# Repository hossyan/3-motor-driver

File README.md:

# 3-motor-driver
PWM信号を送ってモータを一つ動かすための回路です。
大きめの電流が流れる線が細いため、焼ききれる可能性がある。

ゲートドライバの回路の参考になったURLを以下に貼る。

[ゲートドライバ参考](https://www.youtube.com/watch?v=LvKE3vxPTeQ&t=596s)

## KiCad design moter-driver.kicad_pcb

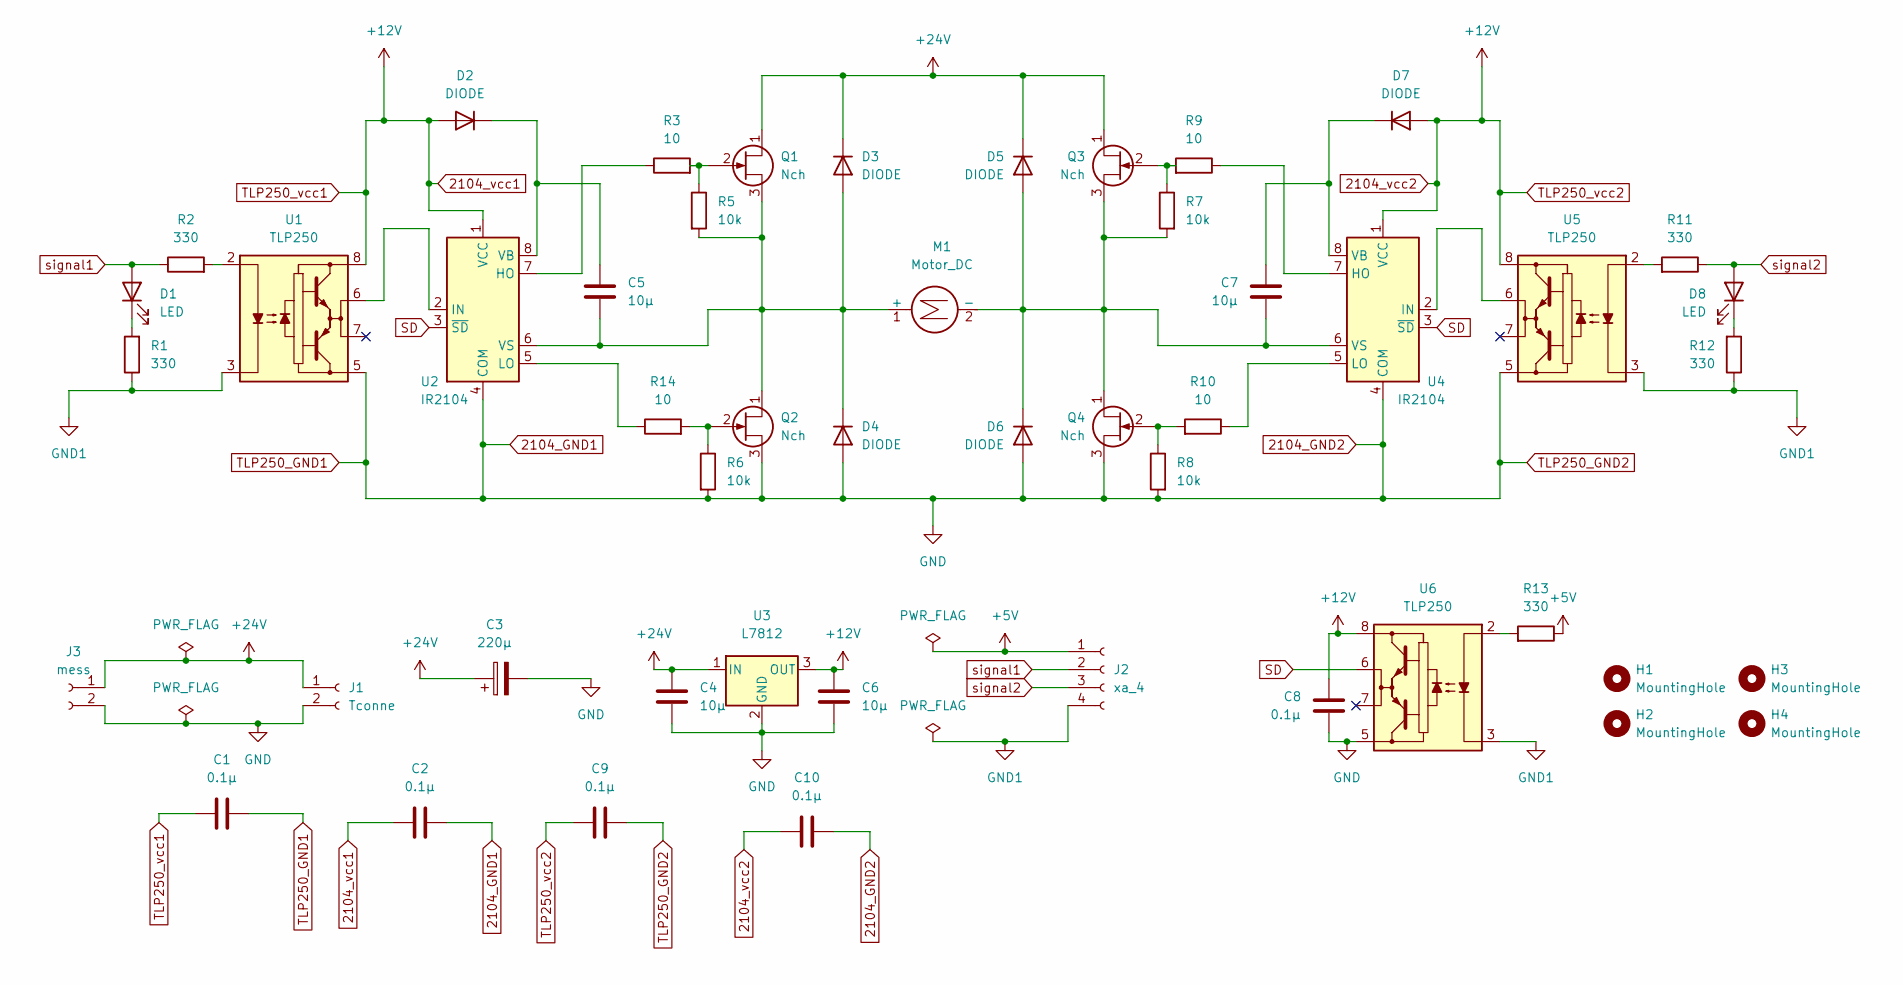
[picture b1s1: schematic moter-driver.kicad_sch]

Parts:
C1, C2, C8, C9, C10: 0.1μ; C_0603_1608Metric
C3: 220μ; CP_Elec_10x10
C4, C5, C6, C7: 10μ; C_0805_2012Metric
D1, D8: LED; LED_D5.0mm
D2, D3, D4, D5, D6, D7: DIODE; D_SOD-123
H1, H2, H3, H4: MountingHole; MountingHole_3.2mm_M3_Pad_Via
J1: Tconne; T_connecter_female_horizontal
J2: xa_4; S04B-XASK-1
J3: mess; T_connecter_female_horizontal
M1: Motor_DC; T_connecter_female_horizontal
Q1, Q2, Q3, Q4: Nch; TO-220-3_Horizontal_TabUp
R1, R2, R11, R12, R13: 330; R_0603_1608Metric
R3, R9, R10, R14: 10; R_0603_1608Metric
R5, R6, R7, R8: 10k; R_0603_1608Metric
U1, U5, U6: TLP250; DIP-8_W7.62mm
U2, U4: IR2104; SOIC-8_3.9x4.9mm_P1.27mm
U3: L7812; TO-252-2

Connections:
2104_GND1: C1.2, C2.2, C3.2, C4.2, C6.2, C8.1, C9.2, C10.2, D4.1 (A), D6.1 (A), J1.2, J3.2, Q2.3 (S), Q4.3 (S), R6.2, R8.2, U1.5 (VEE), U2.4 (COM), U3.2 (GND), U4.4 (COM), U5.5 (VEE), U6.5 (VEE)
2104_vcc1: C1.1, C2.1, C6.1, C8.2, C9.1, C10.1, D2.1 (A), D7.1 (A), U1.8 (VCC), U2.1 (VCC), U3.3 (OUT), U4.1 (VCC), U5.8 (VCC), U6.8 (VCC)
+5V: J2.1, R13.1
+24V: C3.1, C4.1, D3.2 (K), D5.2 (K), J1.1, J3.1, Q1.1 (D), Q3.1 (D), U3.1 (IN)
GND1: J2.4, R1.1, R12.1, U1.3 (C), U5.3 (C), U6.3 (C)
unnamed: C5.1, D2.2 (K), U2.8 (VB)
unnamed: C5.2, D3.1 (A), D4.2 (K), M1.1 (+), Q1.3 (S), Q2.1 (D), R5.2, U2.6 (VS)
unnamed: C7.1, D7.2 (K), U4.8 (VB)
unnamed: C7.2, D5.1 (A), D6.2 (K), M1.2 (-), Q3.3 (S), Q4.1 (D), R7.2, U4.6 (VS)
unnamed: D1.1 (K), R1.2
unnamed: D8.1 (K), R12.2
unnamed: Q1.2 (G), R3.2, R5.1
unnamed: Q2.2 (G), R6.1, R14.2
unnamed: Q3.2 (G), R7.1, R9.2
unnamed: Q4.2 (G), R8.1, R10.2
unnamed: R2.2, U1.2 (A)
unnamed: R3.1, U2.7 (HO)
unnamed: R9.1, U4.7 (HO)
unnamed: R10.1, U4.5 (LO)
unnamed: R11.2, U5.2 (A)
unnamed: R13.2, U6.2 (A)
unnamed: R14.1, U2.5 (LO)
unnamed: U1.6 (VO), U2.2 (IN)
unnamed: U4.2 (IN), U5.6 (VO)
SD: U2.3 (~SD), U4.3 (~SD), U6.6 (VO)
signal1: D1.2 (A), J2.2, R2.1
signal2: D8.2 (A), J2.3, R11.1

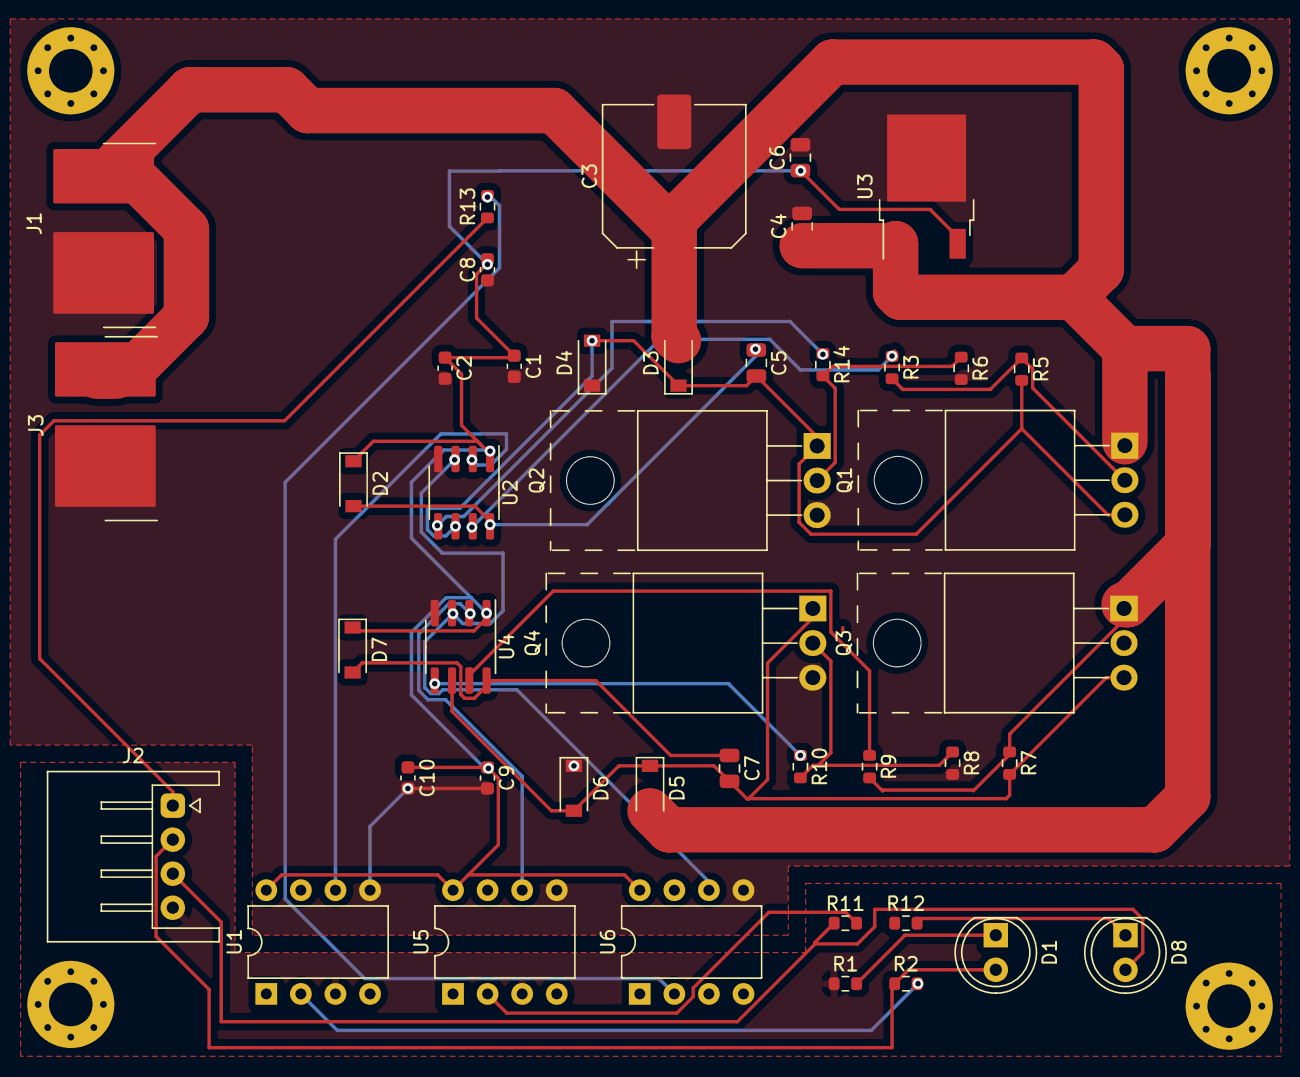
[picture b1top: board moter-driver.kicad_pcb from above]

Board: 2 copper layers, 49 parts (1 on the bottom side), 27 nets.
